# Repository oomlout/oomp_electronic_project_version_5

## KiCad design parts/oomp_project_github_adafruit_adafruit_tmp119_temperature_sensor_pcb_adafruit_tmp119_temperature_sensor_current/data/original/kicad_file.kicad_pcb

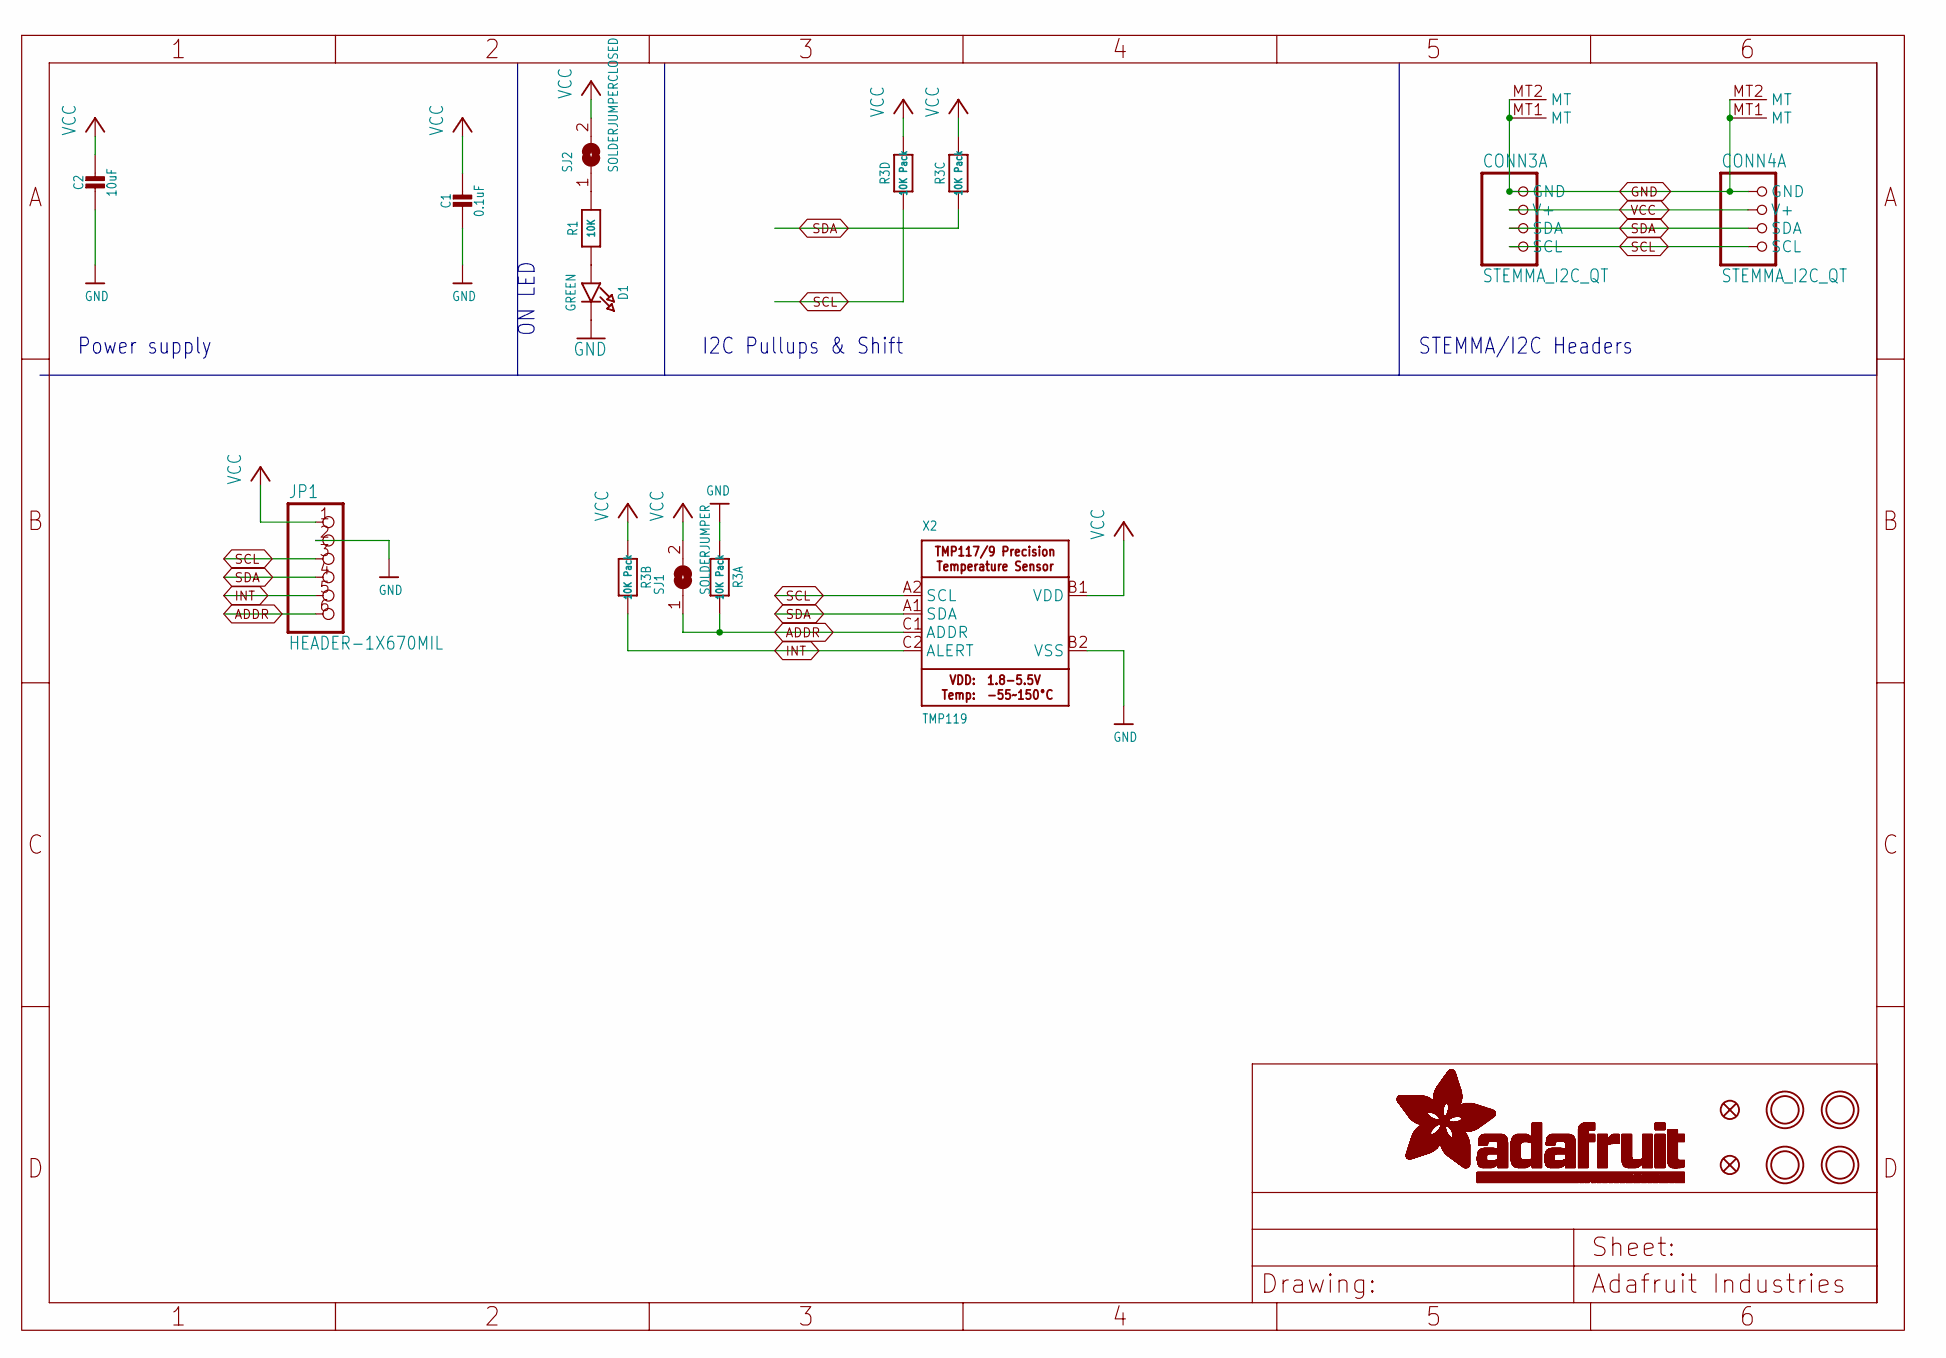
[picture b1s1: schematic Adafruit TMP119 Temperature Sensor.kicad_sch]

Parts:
C1: 0.1uF; 0603-NO
C2: 10uF; 0805-NO
CONN3, CONN4: STEMMA_I2C_QT; JST_SH4; LCSC C2845363
D1: GREEN; CHIPLED_0603_NOOUTLINE
FID3, FID4: FIDUCIAL_0.5MM
JP1: HEADER-1X670MIL; 1X06_ROUND_70
R1: 10K; 0603-NO
R3: 10K Pack; RESPACK_4X0603
SJ1: SOLDERJUMPER; SOLDERJUMPER_ARROW_NOPASTE
SJ2: SOLDERJUMPERCLOSED; SOLDERJUMPER_CLOSEDWIRE
U$1, U$17, U$19, U$21: MOUNTINGHOLE2.5; MOUNTINGHOLE_2.5_PLATED
X2: TMP119; DSBGA-9

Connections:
ADDR: JP1.6, R3.8 (2), SJ1.1, X2.C1 (ADDR)
GND: C1.2, C2.2, CONN3.1 (GND), CONN3.MT1 (MT), CONN3.MT2 (MT), CONN4.1 (GND), CONN4.MT1 (MT), CONN4.MT2 (MT), D1.C, JP1.2, R3.1, X2.B2 (VSS)
INT: JP1.5, R3.7 (2), X2.C2 (ALERT)
unnamed: D1.A, R1.1
unnamed: R1.2, SJ2.1
SCL: CONN3.4 (SCL), CONN4.4 (SCL), JP1.3, R3.4 (1), X2.A2 (SCL)
SDA: CONN3.3 (SDA), CONN4.3 (SDA), JP1.4, R3.3 (1), X2.A1 (SDA)
VCC: C1.1, C2.1, CONN3.2 (V+), CONN4.2 (V+), JP1.1, R3.2 (1), R3.5 (2), R3.6 (2), SJ1.2, SJ2.2, X2.B1 (VDD)

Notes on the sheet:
ON LED
STEMMA/I2C Headers
I2C Pullups & Shift
Power supply

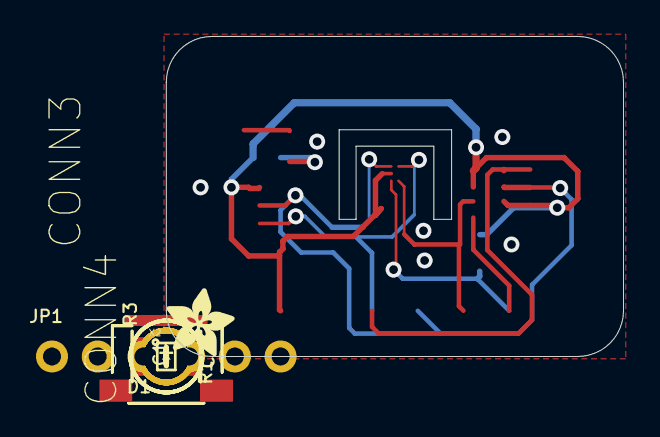
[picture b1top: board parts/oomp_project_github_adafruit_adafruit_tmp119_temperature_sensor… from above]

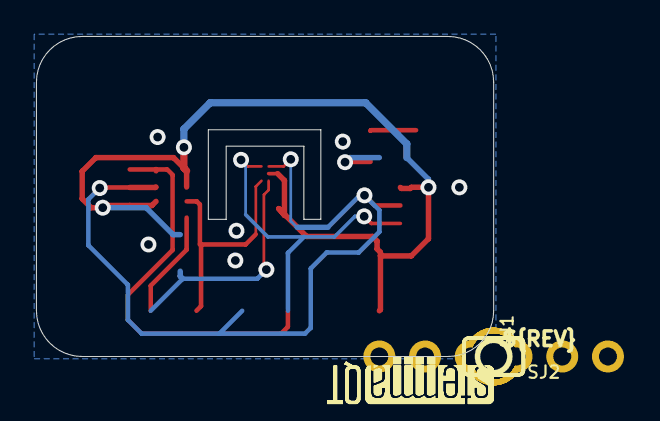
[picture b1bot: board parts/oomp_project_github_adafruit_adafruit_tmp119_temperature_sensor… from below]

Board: 2 copper layers, 25.4 x 17.8 mm, 37 parts (12 on the bottom side), 8 nets.

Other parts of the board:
PLABEL0: PLABEL0
PLABEL1: PLABEL1
PLABEL2: PLABEL2
PLABEL3: PLABEL3
PLABEL4: PLABEL4
PLABEL5: PLABEL5
PLABEL6: PLABEL6
PLABEL7: PLABEL7
PLABEL8: PLABEL8
PLABEL9: PLABEL9
PLABEL10: PLABEL10
PLABEL11: PLABEL11
PLABEL12: PLABEL12
PLABEL13: PLABEL13
PLABEL14: PLABEL14
PLABEL15: PLABEL15
U$22: ADAFRUIT_3.5MM
U$25: PCBFEAT-REV-040
U$30, U$31: STEMMAQT

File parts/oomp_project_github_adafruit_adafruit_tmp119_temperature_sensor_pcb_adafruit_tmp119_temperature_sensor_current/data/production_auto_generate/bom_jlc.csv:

Comment,Designator,Footprint,LCSC Part #
,JP1,Adafruit TMP119 Temperature Sensor-import-fps:1X06_ROUND_70,C37208
,U$22,Adafruit TMP119 Temperature Sensor-import-fps:ADAFRUIT_3.5MM,
,U$25,Adafruit TMP119 Temperature Sensor-import-fps:PCBFEAT-REV-040,
,PLABEL0,Adafruit TMP119 Temperature Sensor-import-fps:PLABEL0,
,PLABEL1,Adafruit TMP119 Temperature Sensor-import-fps:PLABEL1,
,PLABEL10,Adafruit TMP119 Temperature Sensor-import-fps:PLABEL10,
,PLABEL11,Adafruit TMP119 Temperature Sensor-import-fps:PLABEL11,
,PLABEL12,Adafruit TMP119 Temperature Sensor-import-fps:PLABEL12,
,PLABEL13,Adafruit TMP119 Temperature Sensor-import-fps:PLABEL13,
,PLABEL14,Adafruit TMP119 Temperature Sensor-import-fps:PLABEL14,
,PLABEL15,Adafruit TMP119 Temperature Sensor-import-fps:PLABEL15,
,PLABEL2,Adafruit TMP119 Temperature Sensor-import-fps:PLABEL2,
,PLABEL3,Adafruit TMP119 Temperature Sensor-import-fps:PLABEL3,
,PLABEL4,Adafruit TMP119 Temperature Sensor-import-fps:PLABEL4,
,PLABEL5,Adafruit TMP119 Temperature Sensor-import-fps:PLABEL5,
,PLABEL6,Adafruit TMP119 Temperature Sensor-import-fps:PLABEL6,
,PLABEL7,Adafruit TMP119 Temperature Sensor-import-fps:PLABEL7,
,PLABEL8,Adafruit TMP119 Temperature Sensor-import-fps:PLABEL8,
,PLABEL9,Adafruit TMP119 Temperature Sensor-import-fps:PLABEL9,
,"U$30,U$31",Adafruit TMP119 Temperature Sensor-import-fps:STEMMAQT,
0.1uF,C1,Adafruit TMP119 Temperature Sensor-import-fps:0603-NO,C14663
10K,R1,Adafruit TMP119 Temperature Sensor-import-fps:0603-NO,C98220
10K Pack,R3,Adafruit TMP119 Temperature Sensor-import-fps:RESPACK_4X0603,C98220
10uF,C2,Adafruit TMP119 Temperature Sensor-import-fps:0805-NO,
GREEN,D1,Adafruit TMP119 Temperature Sensor-import-fps:CHIPLED_0603_NOOUTLINE,
STEMMA_I2C_QT,"CONN3,CONN4",Adafruit TMP119 Temperature Sensor-import-fps:JST_SH4,C160404
TMP119,X2,Adafruit TMP119 Temperature Sensor-import-fps:DSBGA-9,

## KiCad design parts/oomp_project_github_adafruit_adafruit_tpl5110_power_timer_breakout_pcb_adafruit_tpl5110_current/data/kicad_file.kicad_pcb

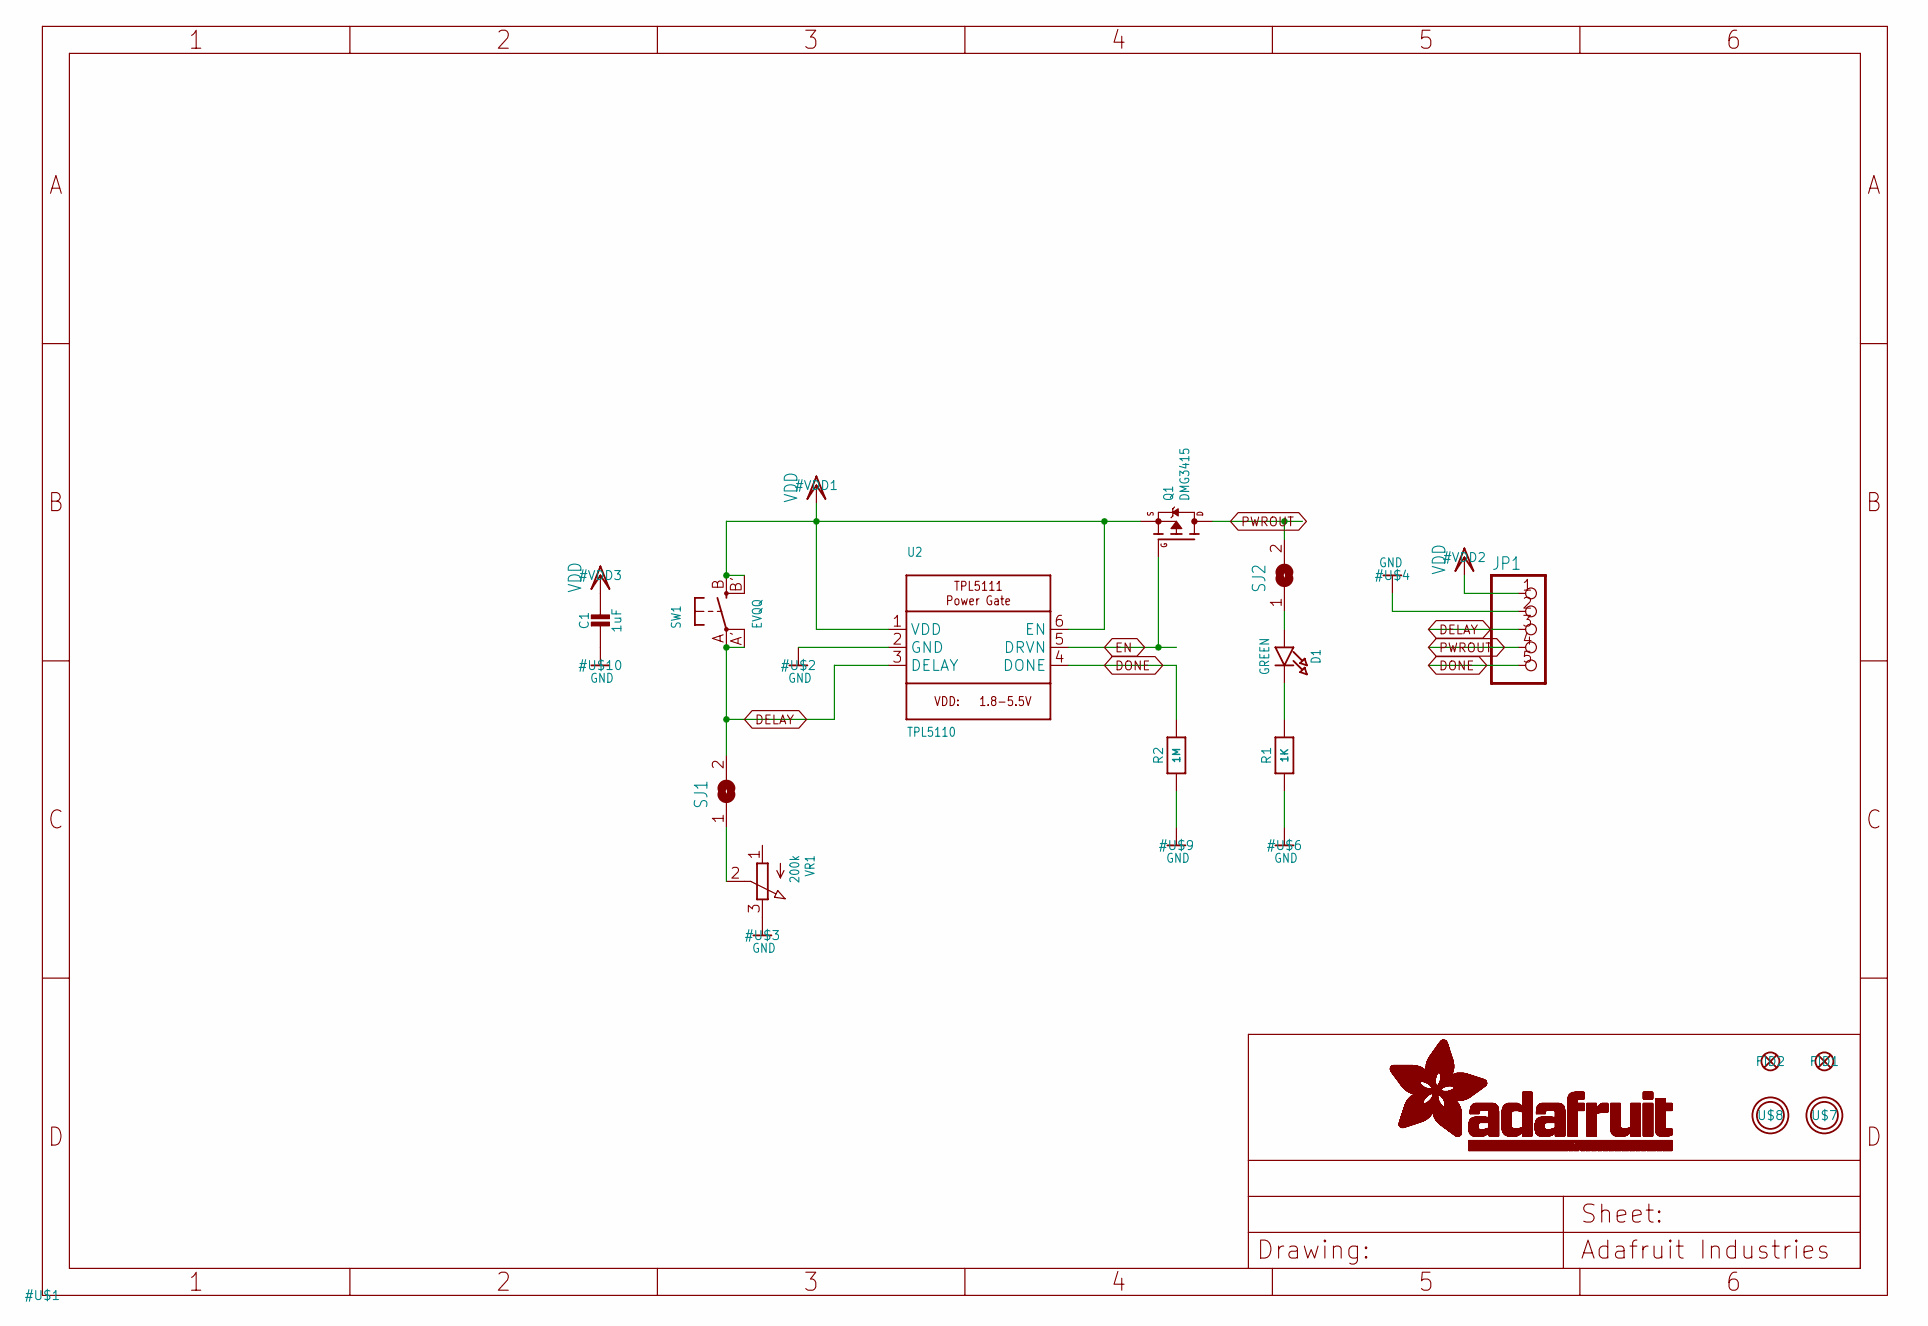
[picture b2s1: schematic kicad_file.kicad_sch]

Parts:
C1: 1uF; 0805-NO
D1: GREEN; CHIPLED_0805_NOOUTLINE
FID1, FID2: FIDUCIAL""; FIDUCIAL_1MM
JP1: HEADER-1X570MIL; 1X05_ROUND_70
Q1: DMG3415; SOT23-WIDE
R1: 1K; 0805-NO
R2: 1M; 0805-NO
SJ1, SJ2: SOLDERJUMPERCLOSED; SOLDERJUMPER_CLOSEDWIRE
SW1: EVQQ; EVQ-Q2_SMALLER
U2: TPL5110; SOT23-6
U$7, U$8: MOUNTINGHOLE2.5; MOUNTINGHOLE_2.5_PLATED
VR1: 200k; TRIMPOT_BOURNS_TC33X-2

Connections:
DELAY: JP1.3, SJ1.2, SW1.A, SW1.A' (P1), U2.3 (DELAY)
DONE: JP1.5, R2.2, U2.4 (DONE)
EN: Q1.1 (G), U2.5 (DRVN)
GND: C1.2, JP1.2, R1.1, R2.1, U2.2 (GND), VR1.3 (E)
unnamed: SJ1.1, VR1.2 (S)
unnamed: D1.A, SJ2.1
unnamed: D1.C, R1.2
PWROUT: JP1.4, Q1.3 (D), SJ2.2
VDD: C1.1, JP1.1, Q1.2 (S), SW1.B (S), SW1.B' (S1), U2.1 (VDD), U2.6 (EN)

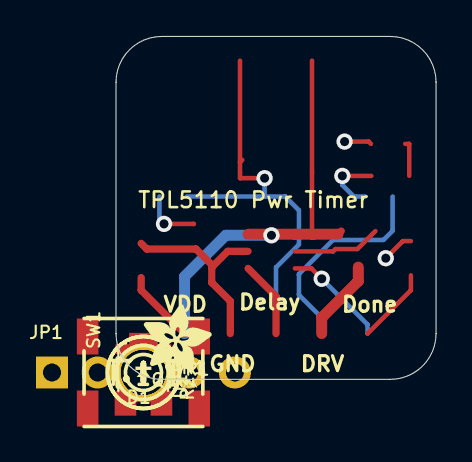
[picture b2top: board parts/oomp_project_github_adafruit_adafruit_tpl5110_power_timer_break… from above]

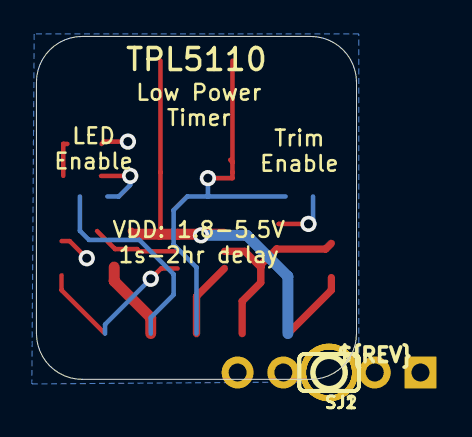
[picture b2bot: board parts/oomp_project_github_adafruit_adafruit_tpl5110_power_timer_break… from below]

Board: 2 copper layers, 17.8 x 19.1 mm, 17 parts (3 on the bottom side), 9 nets.

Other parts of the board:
U$5: ADAFRUIT_3.5MM
U$11: PCBFEAT-REV-040

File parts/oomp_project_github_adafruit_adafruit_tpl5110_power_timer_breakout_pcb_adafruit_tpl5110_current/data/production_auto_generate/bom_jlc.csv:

Comment,Designator,Footprint,LCSC Part #
,JP1,Adafruit TPL5110-import-fps:1X05_ROUND_70,C42431835
,U$5,Adafruit TPL5110-import-fps:ADAFRUIT_3.5MM,
,U$11,Adafruit TPL5110-import-fps:PCBFEAT-REV-040,
1K,R1,Adafruit TPL5110-import-fps:0805-NO,C17513
1M,R2,Adafruit TPL5110-import-fps:0805-NO,C2933280
1uF,C1,Adafruit TPL5110-import-fps:0805-NO,
200k,VR1,Adafruit TPL5110-import-fps:TRIMPOT_BOURNS_TC33X-2,
DMG3415,Q1,Adafruit TPL5110-import-fps:SOT23-WIDE,
EVQQ,SW1,Adafruit TPL5110-import-fps:EVQ-Q2_SMALLER,
GREEN,D1,Adafruit TPL5110-import-fps:CHIPLED_0805_NOOUTLINE,
TPL5110,U2,Adafruit TPL5110-import-fps:SOT23-6,

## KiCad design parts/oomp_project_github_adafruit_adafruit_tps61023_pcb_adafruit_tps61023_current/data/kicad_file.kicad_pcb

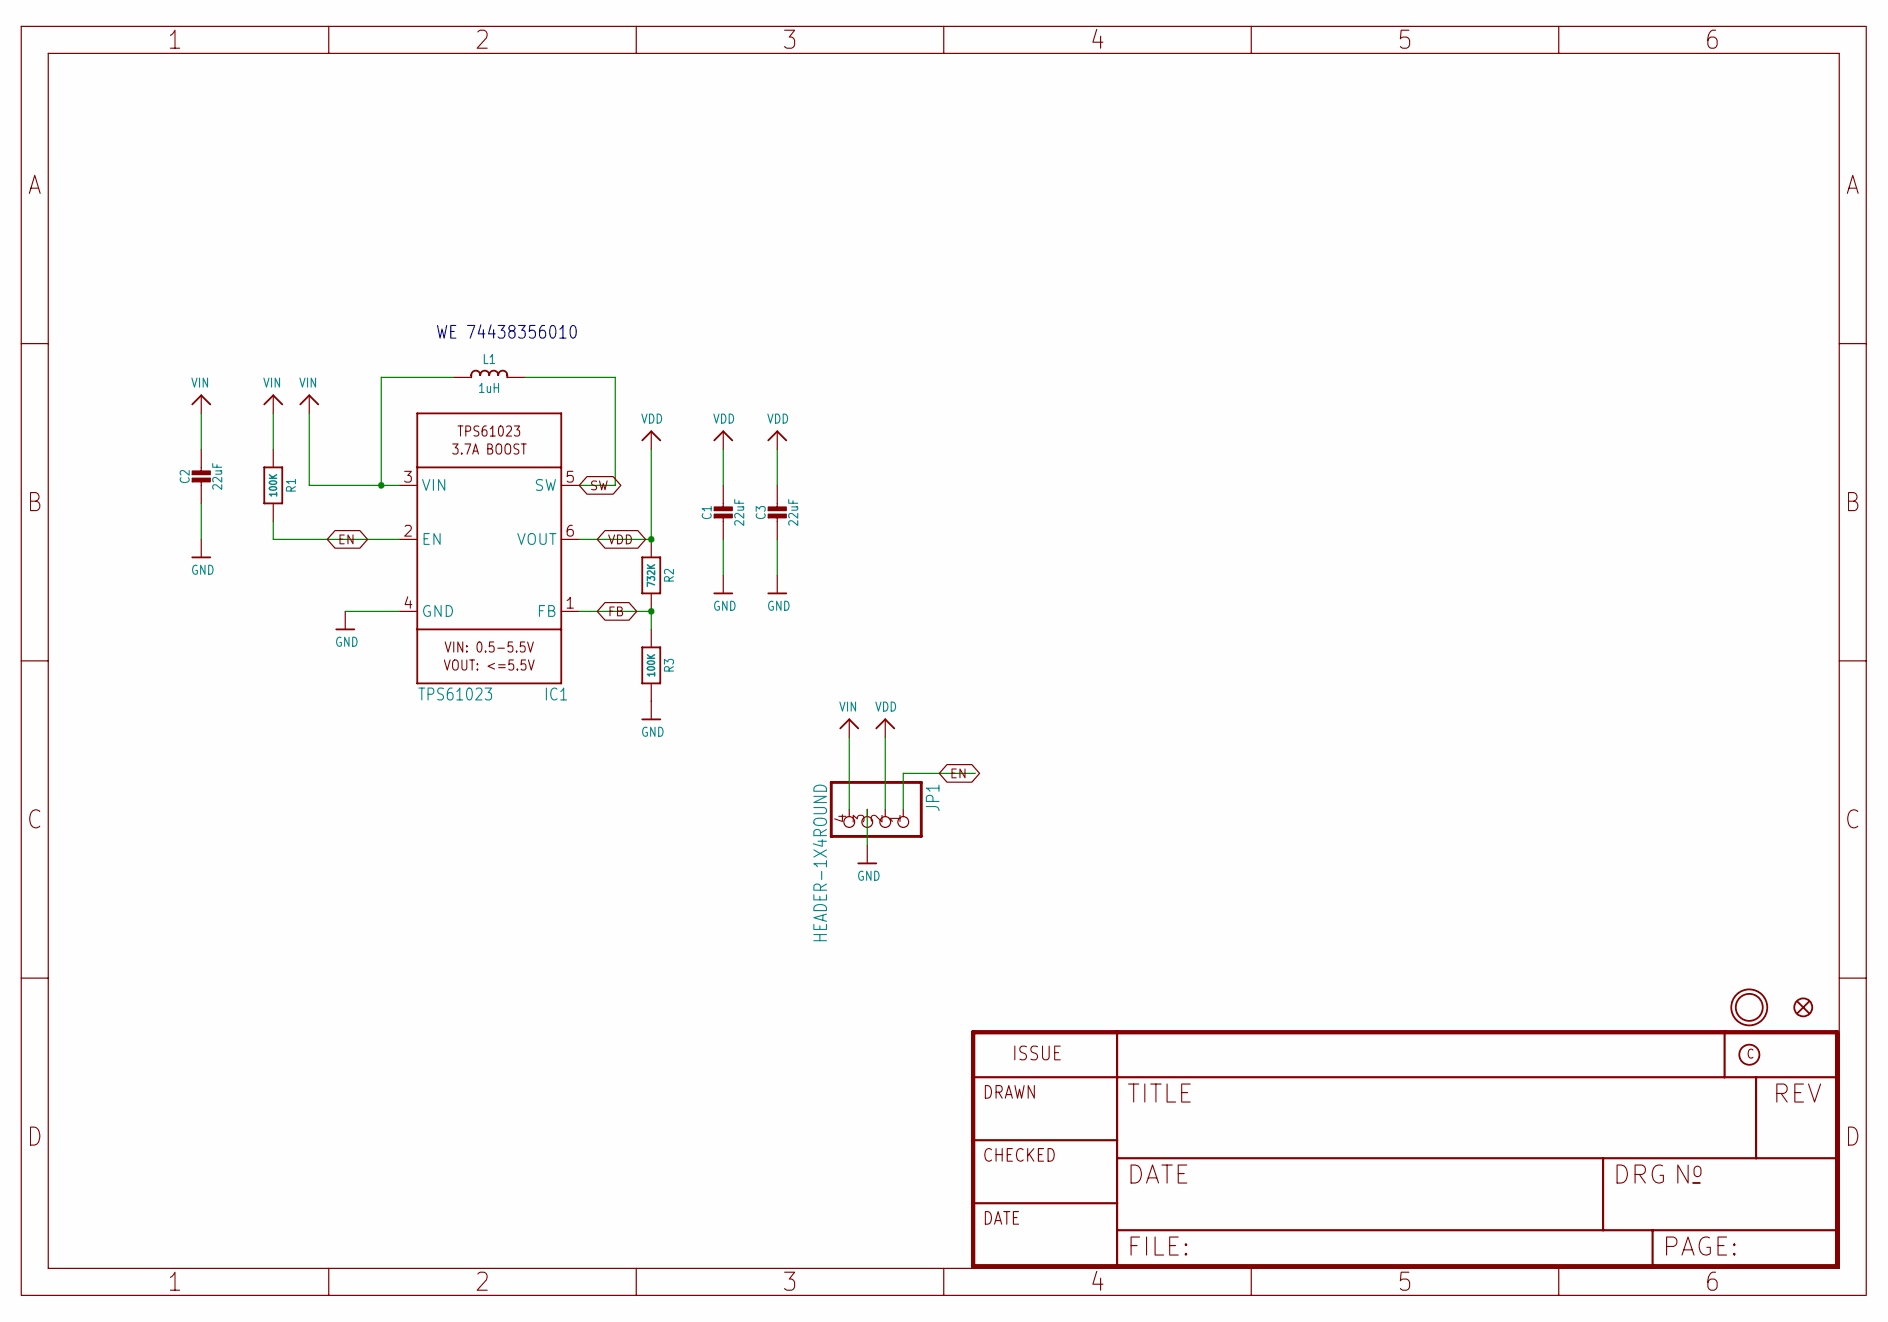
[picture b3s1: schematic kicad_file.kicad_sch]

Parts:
C1, C2, C3: 22uF; 0805-NO
FID1: FIDUCIAL_1MM
IC1: TPS61023; SOT563
JP1: HEADER-1X4ROUND; 1X04_ROUND
L1: 1uH; INDUCTOR_5X5MM_TDK_VLC5045
R1, R3: 100K; 0603-NO
R2: 732K; 0603-NO
U$9: MOUNTINGHOLE2.5; MOUNTINGHOLE_2.5_PLATED

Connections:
EN: IC1.2 (EN), JP1.1, R1.2
FB: IC1.1 (FB), R2.2, R3.1
GND: C1.2, C2.2, C3.2, IC1.4 (GND), JP1.3, R3.2
SW: IC1.5 (SW), L1.P$2 (2)
VDD: C1.1, C3.1, IC1.6 (VOUT), JP1.2, R2.1
VIN: C2.1, IC1.3 (VIN), JP1.4, L1.P$1 (1), R1.1

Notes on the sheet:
WE 74438356010

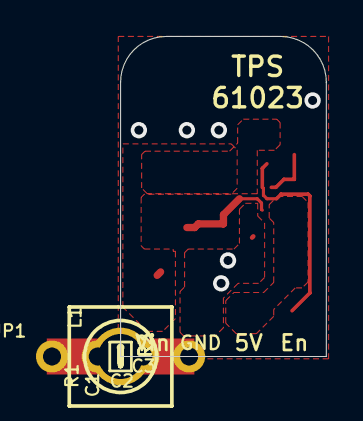
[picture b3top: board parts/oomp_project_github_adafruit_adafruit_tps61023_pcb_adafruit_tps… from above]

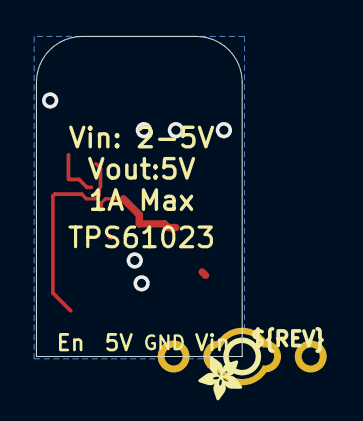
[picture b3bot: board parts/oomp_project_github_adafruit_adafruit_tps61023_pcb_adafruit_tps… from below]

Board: 2 copper layers, 11.4 x 17.8 mm, 13 parts (2 on the bottom side), 6 nets.

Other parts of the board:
U$10: PCBFEAT-REV-040
U$11: ADAFRUIT_2.5MM

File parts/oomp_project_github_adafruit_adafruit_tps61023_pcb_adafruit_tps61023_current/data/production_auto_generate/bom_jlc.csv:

Comment,Designator,Footprint,LCSC Part #
,JP1,Adafruit TPS61023-import-fps:1X04_ROUND,C42431795
,U$11,Adafruit TPS61023-import-fps:ADAFRUIT_2.5MM,
,U$10,Adafruit TPS61023-import-fps:PCBFEAT-REV-040,
100K,"R1,R3",Adafruit TPS61023-import-fps:0603-NO,C25803
1uH,L1,Adafruit TPS61023-import-fps:INDUCTOR_5X5MM_TDK_VLC5045,
22uF,"C1,C2,C3",Adafruit TPS61023-import-fps:0805-NO,
732K,R2,Adafruit TPS61023-import-fps:0603-NO,
TPS61023,IC1,Adafruit TPS61023-import-fps:SOT563,

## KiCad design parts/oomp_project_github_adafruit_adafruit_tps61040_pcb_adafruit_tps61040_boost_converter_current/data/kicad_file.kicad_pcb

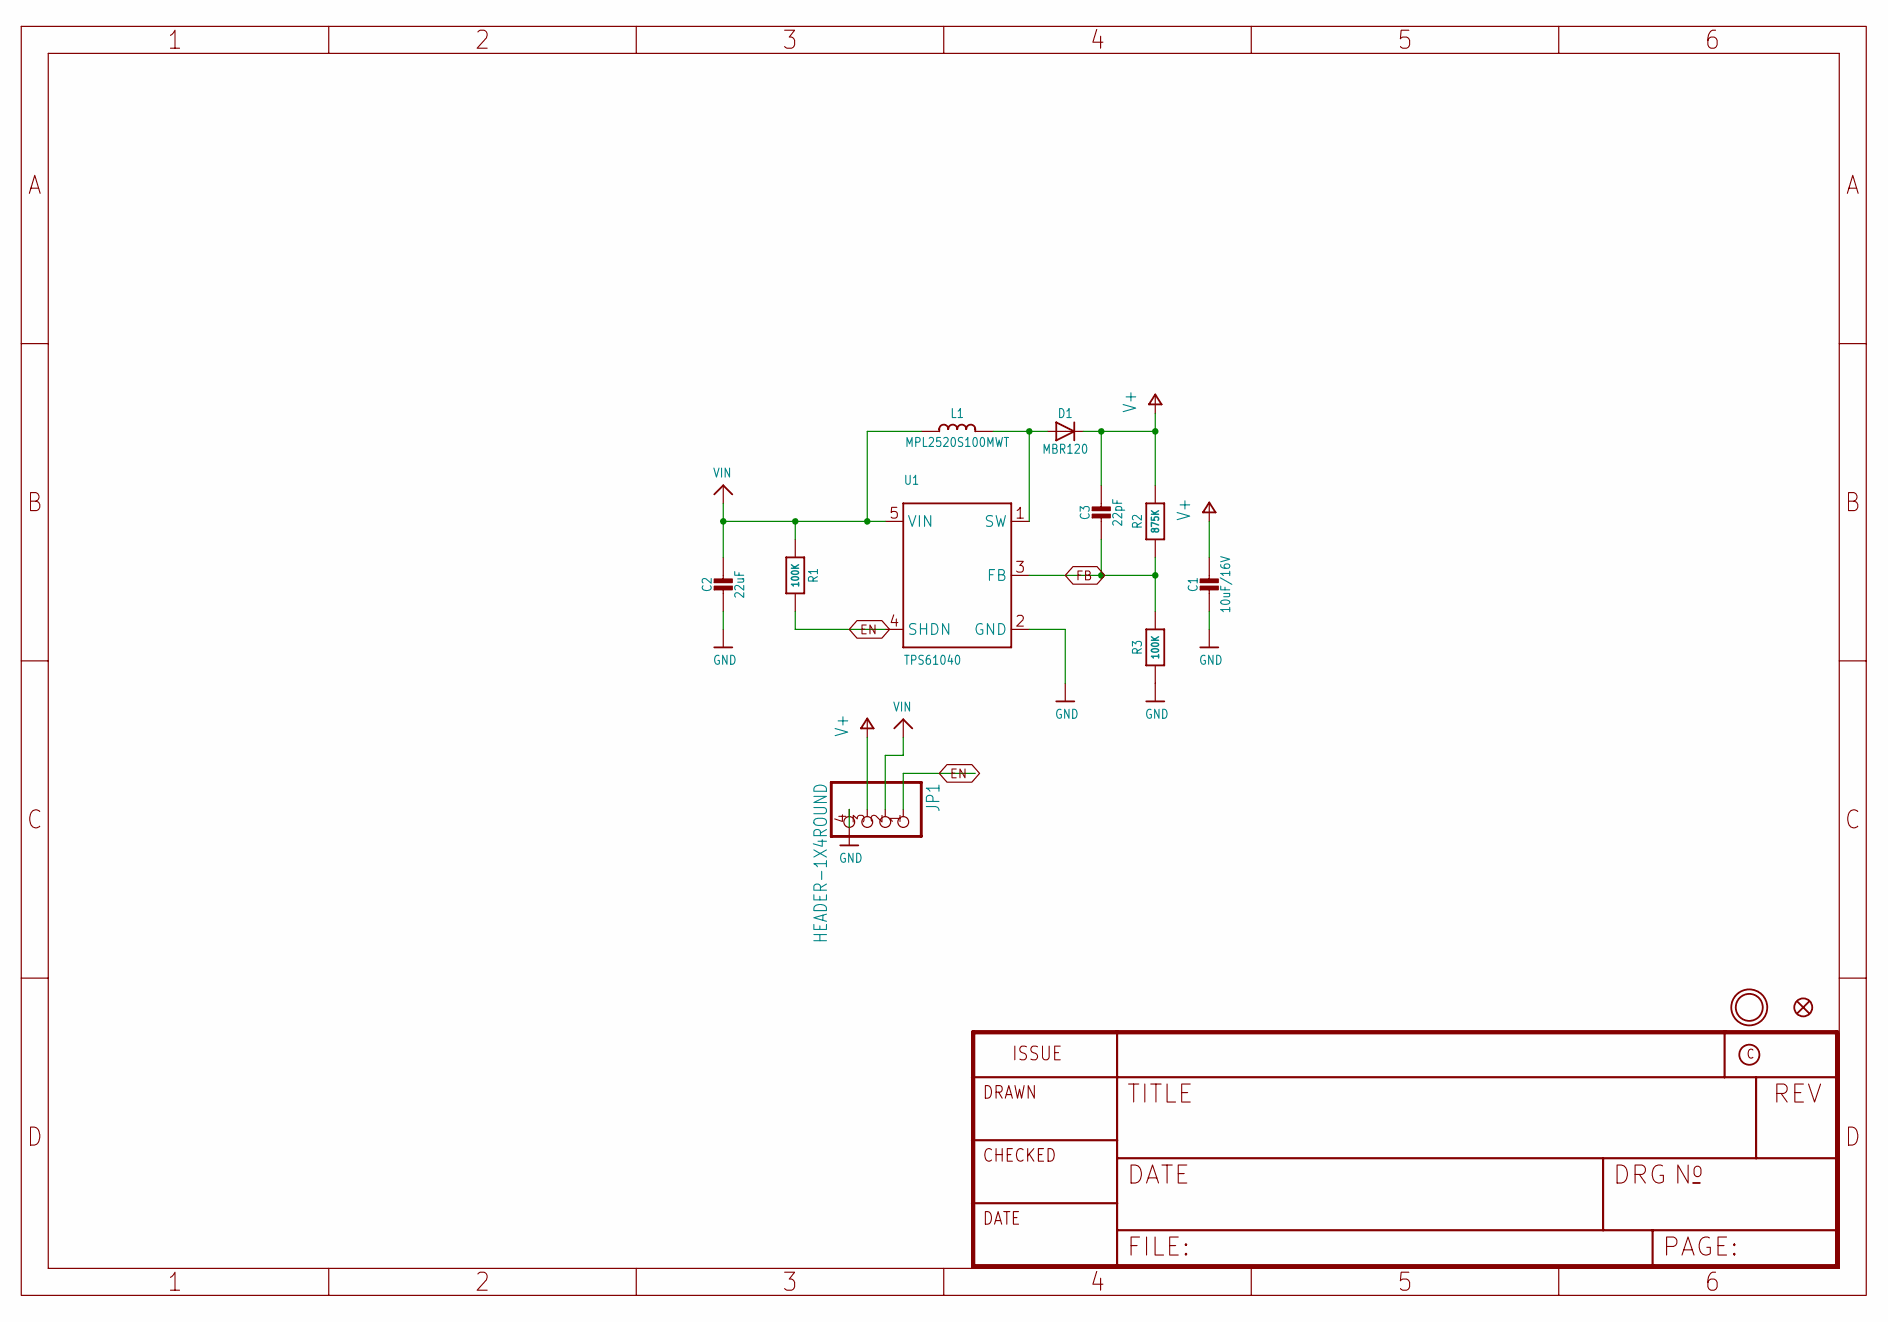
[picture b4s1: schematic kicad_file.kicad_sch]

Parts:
C1: 10uF/16V; 0805-NO
C2: 22uF; 0805-NO
C3: 22pF; 0603-NO
D1: MBR120; SOD-123FL
FID1: FIDUCIAL_1MM
JP1: HEADER-1X4ROUND; 1X04_ROUND
L1: MPL2520S100MWT; INDUCTOR_1007
R1, R3: 100K; 0603-NO
R2: 875K; 0603-NO
U1: TPS61040; SOT23-5
U$9: MOUNTINGHOLE2.5; MOUNTINGHOLE_2.5_PLATED

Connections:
EN: JP1.1, R1.2, U1.4 (SHDN)
FB: C3.2, R2.1, R3.2, U1.3 (FB)
GND: C1.2, C2.2, JP1.4, R3.1, U1.2 (GND)
unnamed: D1.A, L1.P$2 (2), U1.1 (SW)
V+: C1.1, C3.1, D1.C, JP1.3, R2.2
VIN: C2.1, JP1.2, L1.P$1 (1), R1.1, U1.5 (VIN)

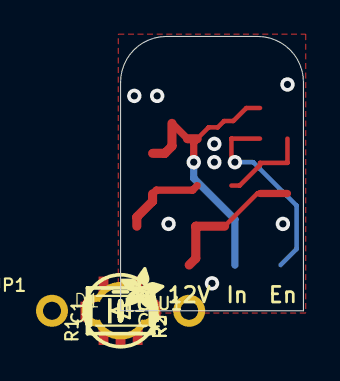
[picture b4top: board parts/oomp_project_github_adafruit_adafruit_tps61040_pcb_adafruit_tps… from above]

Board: 2 copper layers, 10.2 x 15.2 mm, 14 parts (1 on the bottom side), 6 nets.

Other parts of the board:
U$10: PCBFEAT-REV-040
U$11: ADAFRUIT_2.5MM

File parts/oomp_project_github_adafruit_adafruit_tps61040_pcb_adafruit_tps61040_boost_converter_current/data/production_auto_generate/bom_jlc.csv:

Comment,Designator,Footprint,LCSC Part #
,JP1,Adafruit TPS61040 Boost Converter-import-fps:1X04_ROUND,C42431795
,U$11,Adafruit TPS61040 Boost Converter-import-fps:ADAFRUIT_2.5MM,
,U$10,Adafruit TPS61040 Boost Converter-import-fps:PCBFEAT-REV-040,
100K,"R1,R3",Adafruit TPS61040 Boost Converter-import-fps:0603-NO,C25803
10uF/16V,C1,Adafruit TPS61040 Boost Converter-import-fps:0805-NO,
22pF,C3,Adafruit TPS61040 Boost Converter-import-fps:0603-NO,C105620
22uF,C2,Adafruit TPS61040 Boost Converter-import-fps:0805-NO,
875K,R2,Adafruit TPS61040 Boost Converter-import-fps:0603-NO,
MBR120,D1,Adafruit TPS61040 Boost Converter-import-fps:SOD-123FL,
MPL2520S100MWT,L1,Adafruit TPS61040 Boost Converter-import-fps:INDUCTOR_1007,
TPS61040,U1,Adafruit TPS61040 Boost Converter-import-fps:SOT23-5,

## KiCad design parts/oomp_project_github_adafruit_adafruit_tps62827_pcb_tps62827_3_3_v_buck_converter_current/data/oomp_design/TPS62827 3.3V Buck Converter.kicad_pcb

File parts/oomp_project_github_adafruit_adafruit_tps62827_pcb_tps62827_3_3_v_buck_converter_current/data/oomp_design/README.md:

# OOMP KiCad design copy

Open `TPS62827 3.3V Buck Converter.kicad_pro` (or the `.kicad_pcb` / `.kicad_sch`) in KiCad. Local OOMP libraries are under `libraries/`. Original inputs are preserved in [../original/](../original/).

Only verified unchanged installed KiCad defaults were renamed. Modified, custom, unmatched and unavailable items remain unchanged. Soldering variants are never swapped during conversion. Existing pad coordinates, nets and UUIDs are preserved.

See [conversion_report.yaml](conversion_report.yaml) for every conversion and skip. Copy this directory before editing; regeneration refuses to overwrite edited design files.

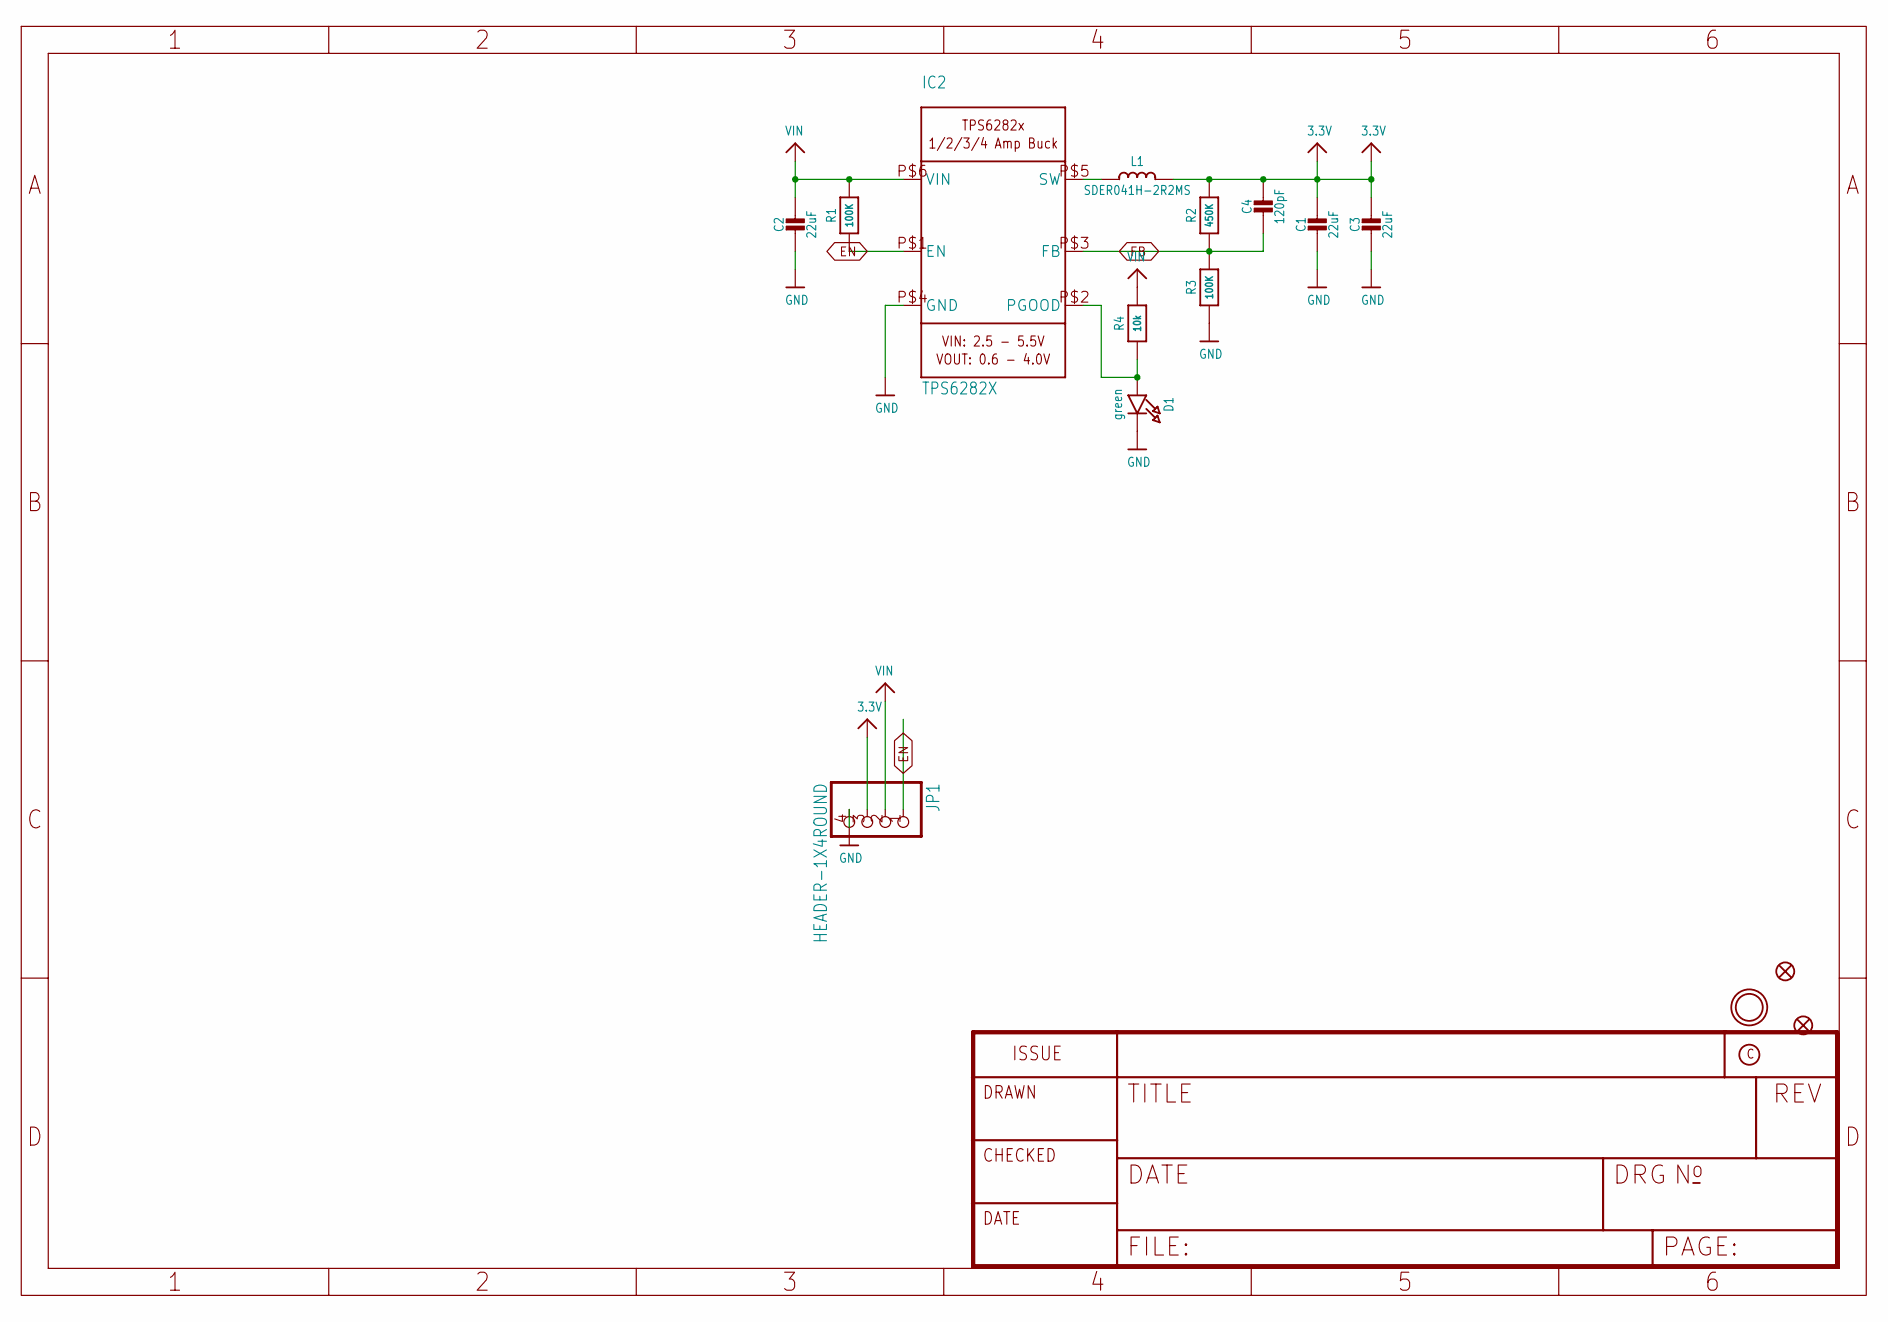
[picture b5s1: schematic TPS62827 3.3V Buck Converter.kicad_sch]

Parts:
C1, C2, C3: 22uF; 0805-NO
C4: 120pF; 0603-NO
D1: green; CHIPLED_0603_NOOUTLINE
FID1, FID2: FIDUCIAL_1MM
IC2: TPS6282X; VSON_6
JP1: HEADER-1X4ROUND; 1X04_ROUND
L1: SDER041H-2R2MS; INDUCTOR_4X4MM_SRP0415
R1, R3: 100K; 0603-NO
R2: 450K; 0603-NO
R4: 10k; _0603MP
U$9: MOUNTINGHOLE2.5; MOUNTINGHOLE_2.5_PLATED

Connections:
3.3V: C1.1, C3.1, C4.1, JP1.3, L1.P$2 (2), R2.2
EN: IC2.P$1 (EN), JP1.1, R1.2
FB: C4.2, IC2.P$3 (FB), R2.1, R3.2
GND: C1.2, C2.2, C3.2, D1.C, IC2.P$4 (GND), JP1.4, R3.1
unnamed: IC2.P$5 (SW), L1.P$1 (1)
unnamed: D1.A, IC2.P$2 (PGOOD), R4.1
VIN: C2.1, IC2.P$6 (VIN), JP1.2, R1.1, R4.2

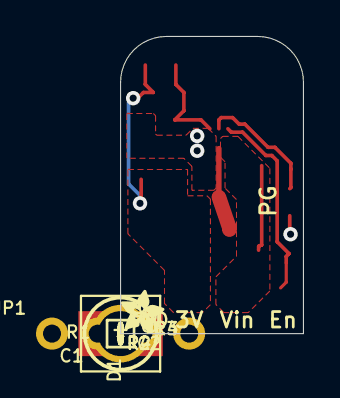
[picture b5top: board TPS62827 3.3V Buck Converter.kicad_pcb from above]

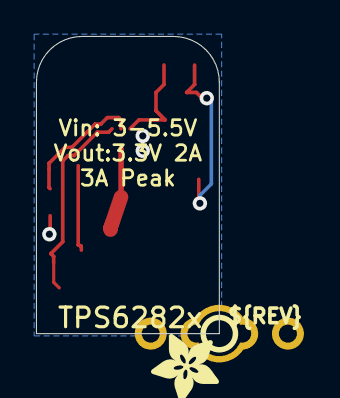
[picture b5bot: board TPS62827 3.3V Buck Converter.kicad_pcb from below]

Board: 2 copper layers, 10.2 x 16.5 mm, 18 parts (2 on the bottom side), 7 nets.

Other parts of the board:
U$10: PCBFEAT-REV-040
U$11: ADAFRUIT_2.5MM
U$18: ADAFRUIT_3.5MM

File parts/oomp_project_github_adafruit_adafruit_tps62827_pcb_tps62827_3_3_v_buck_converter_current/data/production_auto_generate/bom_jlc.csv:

Comment,Designator,Footprint,LCSC Part #
,JP1,TPS62827 3.3V Buck Converter-import-fps:1X04_ROUND,C42431795
,U$11,TPS62827 3.3V Buck Converter-import-fps:ADAFRUIT_2.5MM,
,U$18,TPS62827 3.3V Buck Converter-import-fps:ADAFRUIT_3.5MM,
,U$10,TPS62827 3.3V Buck Converter-import-fps:PCBFEAT-REV-040,
100K,"R1,R3",TPS62827 3.3V Buck Converter-import-fps:0603-NO,C25803
10k,R4,TPS62827 3.3V Buck Converter-import-fps:_0603MP,C98220
120pF,C4,TPS62827 3.3V Buck Converter-import-fps:0603-NO,
22uF,"C1,C2,C3",TPS62827 3.3V Buck Converter-import-fps:0805-NO,
450K,R2,TPS62827 3.3V Buck Converter-import-fps:0603-NO,
green,D1,TPS62827 3.3V Buck Converter-import-fps:CHIPLED_0603_NOOUTLINE,
SDER041H-2R2MS,L1,TPS62827 3.3V Buck Converter-import-fps:INDUCTOR_4X4MM_SRP0415,
TPS6282X,IC2,TPS62827 3.3V Buck Converter-import-fps:VSON_6,
